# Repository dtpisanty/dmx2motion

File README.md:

# dmx2motion
An ESP32 based open-hardware project to control varing frequency AC motror drivers through DMX, ArtNet, OSC and MQTT

## Circuit board files
Schematics and PCB files were created using DIP Trace

## Library dependencies
This project uses Lukas Salomons ESP32-DMX Library https://github.com/luksal/ESP32-DMX and ThingPulse's ssd1306 OLED driver https://github.com/ThingPulse/esp8266-oled-ssd1306

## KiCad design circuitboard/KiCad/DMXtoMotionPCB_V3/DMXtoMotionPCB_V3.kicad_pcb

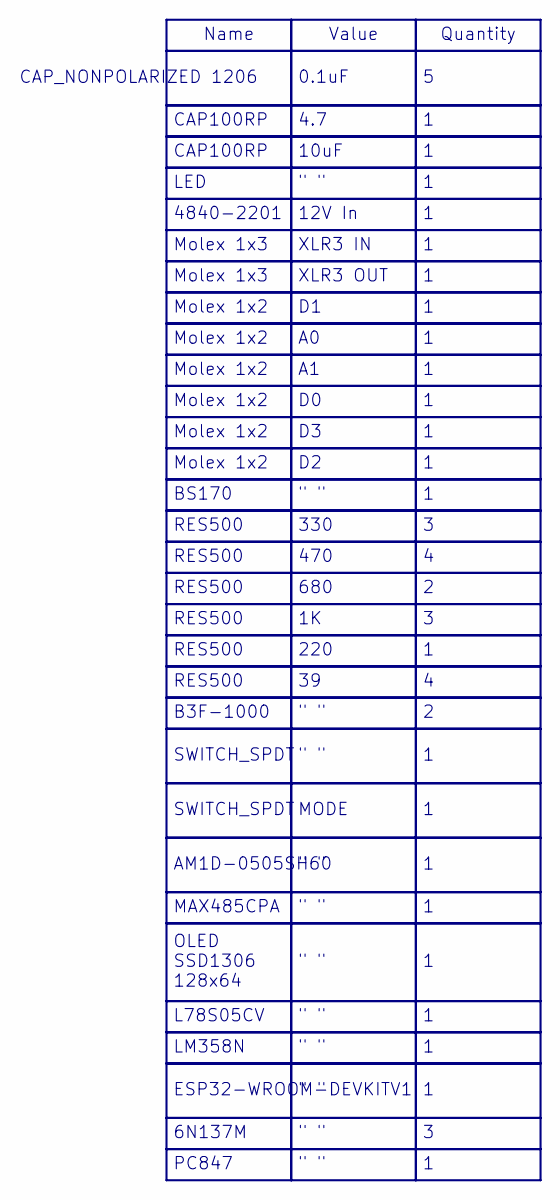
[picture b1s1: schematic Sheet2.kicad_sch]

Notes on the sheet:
Molex 1x2
" "
CAP100RP
470
L78S05CV
Molex 1x3
6N137M
Name
4840-2201
MAX485CPA
CAP_NONPOLARIZED 1206
RES500
4.7
Value
10uF
B3F-1000
AM1D-0505SH60
LM358N
330
PC847
680
220
0.1uF
LED
SWITCH_SPDT
XLR3 OUT
BS170
12V In
Quantity
MODE
XLR3 IN
OLED SSD1306 128x64
ESP32-WROOM-DEVKITV1

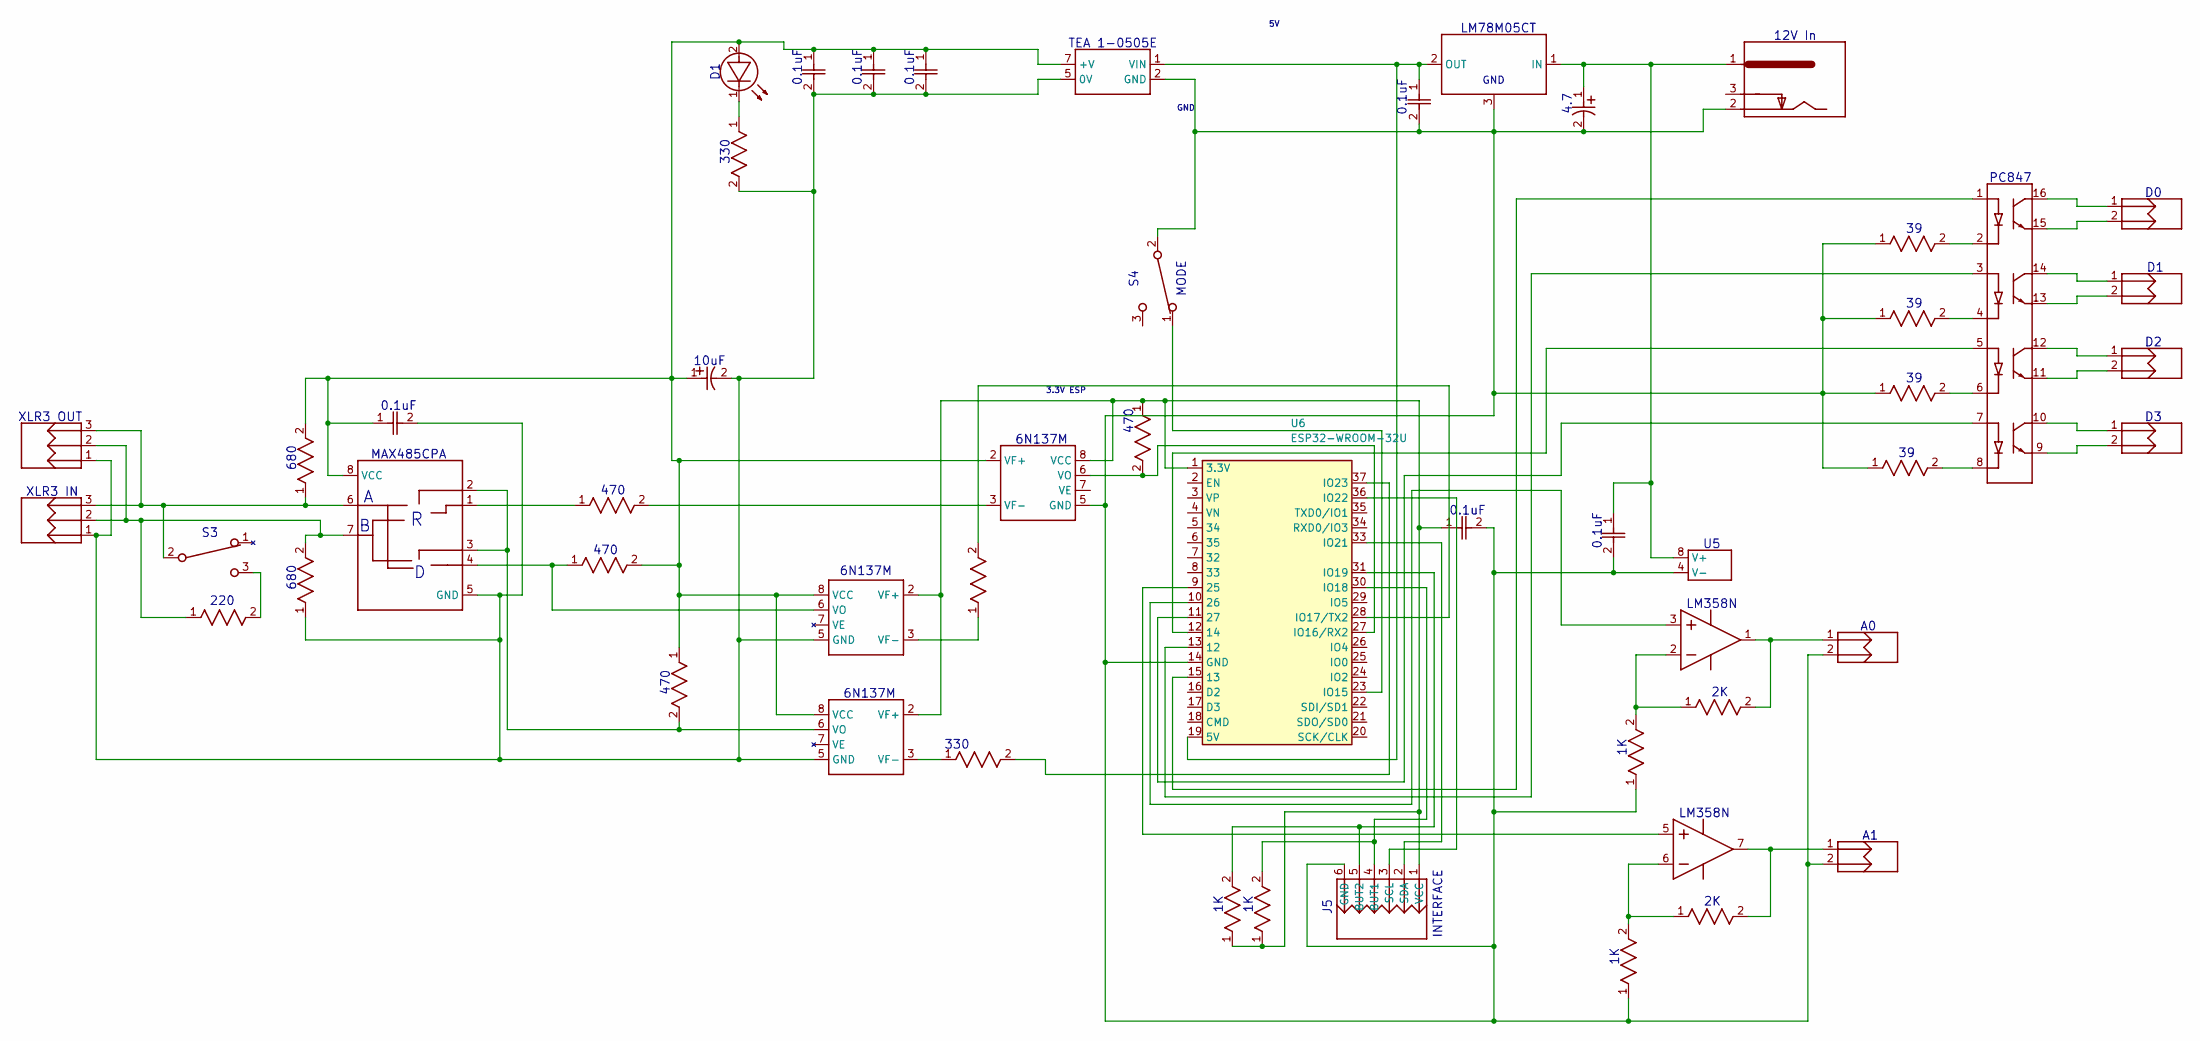
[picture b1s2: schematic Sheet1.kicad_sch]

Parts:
C1, C2, C3, C6, C7, C8, C9: 0.1uF; C_1206_3216Metric_Pad1.33x1.80mm_HandSolder
C4: 4.7; CP_Elec_4x5.3
C5: 10uF; CP_Elec_4x5.3
D1: LED; LED100
J1: 12V In; BarrelJack_Horizontal
J2: XLR3 IN; HDR-1X3
J3: XLR3 OUT; HDR-1X3
J4: D1; HDR-1X2
J5: INTERFACE; HDR-1X6
J6: A0; HDR-1X2
J7: A1; HDR-1X2
J8: D0; HDR-1X2
J9: D3; HDR-1X2
J10: D2; HDR-1X2
R1, R2, R3: 330; R_1206_3216Metric_Pad1.30x1.75mm_HandSolder
R4, R5, R6, R13: 470; R_1206_3216Metric_Pad1.30x1.75mm_HandSolder
R7, R8: 680; R_1206_3216Metric_Pad1.30x1.75mm_HandSolder
R9, R10, R18, R20: 1K; R_1206_3216Metric_Pad1.30x1.75mm_HandSolder
R12: 220; R_1206_3216Metric_Pad1.30x1.75mm_HandSolder
R14, R15, R16, R17: 39; R_1206_3216Metric_Pad1.30x1.75mm_HandSolder
R19, R21: 2K; R_1206_3216Metric_Pad1.30x1.75mm_HandSolder
S3: SWITCH_SPDT; HDRF-1X3T_2.54_8X3
S4: MODE; HDRF-1X3T_2.54_8X3
U1: AM1D-0505SH60; SIP-4(7)_19.5X6X2.54
U2: MAX485CPA; DIP-8
U4: LM78M05CT; TO-220V
U5: LM358N; DIP-8
U6: ESP32-WROOM-32U; ESP32-DevKitC
VO1, VO2, VO3: 6N137M; DIP-8
VO4: PC847; DIP-16

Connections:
3.3V_ESP: C7.1, J5.1 (VCC), R9.1 (A), R10.1 (A), R13.1 (A), U6.1 (3.3V), VO1.8 (VCC), VO2.2 (VF+), VO3.2 (VF+)
5V: C9.1, U1.1 (VIN), U4.2 (OUT), U6.19 (5V)
12V: C4.1 (PLUS), C6.1, J1.1, U4.1 (IN), U5.8 (V+)
But1: J5.4 (BUT1), R10.2 (B), U6.30 (IO18)
But2: J5.5 (BUT2), R9.2 (B), U6.31 (IO19)
GND: C4.2 (MINUS), C6.2, C7.2, C9.2, J1.2, J5.6 (GND), J6.2, J7.2, R14.1 (A), R15.1 (A), R16.1 (A), R17.1 (A), R18.1 (A), R20.1 (A), S4.2 (C1), U1.2 (GND), U4.3 (GND), U5.4 (V-), U6.14 (GND), U6.32 (GND), U6.38 (GND), VO1.5 (GND)
ISO-5V: C1.1, C2.1, C3.1, C5.1 (PLUS), C8.1, D1.2 (A), R5.2 (B), R6.1 (A), R7.2 (B), U1.7 (+V), U2.8 (VCC), VO1.2 (VF+), VO2.8 (VCC), VO3.8 (VCC)
ISO-GND: C1.2, C2.2, C3.2, C5.2 (MINUS), C8.2, J2.1, J3.1, R1.2 (B), R8.1 (A), U1.5 (0V), U2.5 (GND), VO2.5 (GND), VO3.5 (GND)
Net_0: R17.2 (B), VO4.2 (Cathode@1)
Net_1: U6.12 (14), VO4.5 (Anode@3)
Net_2: U6.11 (27), VO4.7 (Anode@4)
Net_4: D1.1 (K), R1.1 (A)
Net_6: U6.15 (13), VO4.1 (Anode@1)
Net_7: U6.13 (12), VO4.3 (Anode@2)
Net_8: U5.5 (IN+), U6.9 (25)
Net_9: R2.1 (A), VO2.3 (VF-)
Net_10: R3.2 (B), U6.37 (IO23)
Net_11: R3.1 (A), VO3.3 (VF-)
Net_12: R4.2 (B), VO1.3 (VF-)
Net_13: R4.1 (A), U2.1 (RO)
Net_14: R6.2 (B), U2.2 (~RE), U2.3 (DE), VO3.6 (VO)
Net_15: R5.1 (A), U2.4 (DI), VO2.6 (VO)
Net_16: J2.2, J3.2, R8.2 (B), R12.1 (A), U2.7 (B)
Net_17: J2.3, J3.3, R7.1 (A), S3.2 (C1), U2.6 (A)
Net_18: J7.1, R19.2 (B), U5.7 (OUT)
Net_21: R18.2 (B), R19.1 (A), U5.6 (IN-)
Net_22: S4.1 (C2), U6.23 (IO15)
Net_24: U5.3 (IN+), U6.10 (26)
Net_32: J5.2 (SDA), U6.33 (IO21)
Net_33: J5.3 (SCL), U6.36 (IO22)
Net_34: R12.2 (B), S3.3 (C3)
Net_35: R14.2 (B), VO4.4 (Cathode@2)
Net_36: R15.2 (B), VO4.6 (Cathode@3)
Net_37: R16.2 (B), VO4.8 (Cathode@4)
Net_38: J8.2, VO4.15 (Emitter@1)
Net_39: J8.1, VO4.16 (Collector@1)
Net_40: J4.1, VO4.14 (Collector@2)
Net_41: J4.2, VO4.13 (Emitter@2)
Net_42: J10.1, VO4.12 (Collector@3)
Net_43: J10.2, VO4.11 (Emitter@3)
Net_44: J9.1, VO4.10 (Collector@4)
Net_45: J9.2, VO4.9 (Emitter@4)
Net_46: J6.1, R21.2 (B), U5.1 (OUT)
Net_47: R20.2 (B), R21.1 (A), U5.2 (IN-)
RX: R13.2 (B), U6.27 (IO16/RX2), VO1.6 (VO)
TX: R2.2 (B), U6.28 (IO17/TX2)

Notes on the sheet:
PC847
330
6N137M
GND
0.1uF
10uF
470
XLR3 IN
XLR3 OUT
LM358N
MODE
TEA 1-0505E
680
INTERFACE
3.3V ESP
12V In
220
LM78M05CT
MAX485CPA
4.7

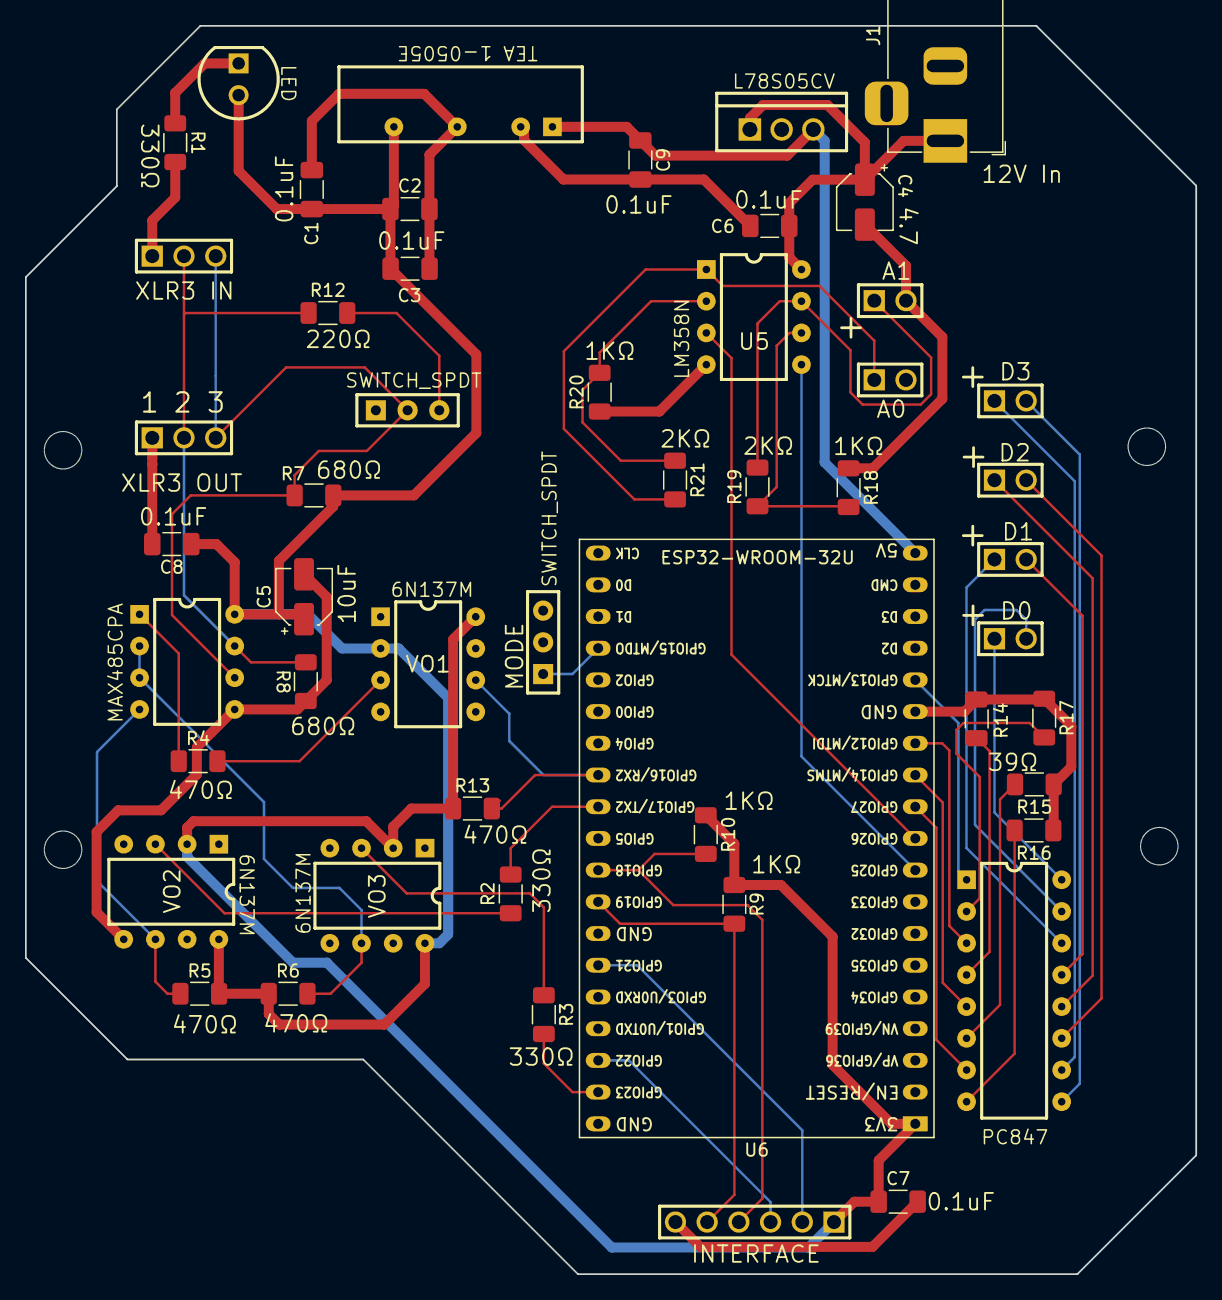
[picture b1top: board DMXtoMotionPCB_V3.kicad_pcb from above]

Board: 2 copper layers, 93.8 x 100.0 mm, 55 parts (0 on the bottom side), 46 nets.

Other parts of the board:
@HOLE0, @HOLE1, @HOLE2, @HOLE3: (no value)

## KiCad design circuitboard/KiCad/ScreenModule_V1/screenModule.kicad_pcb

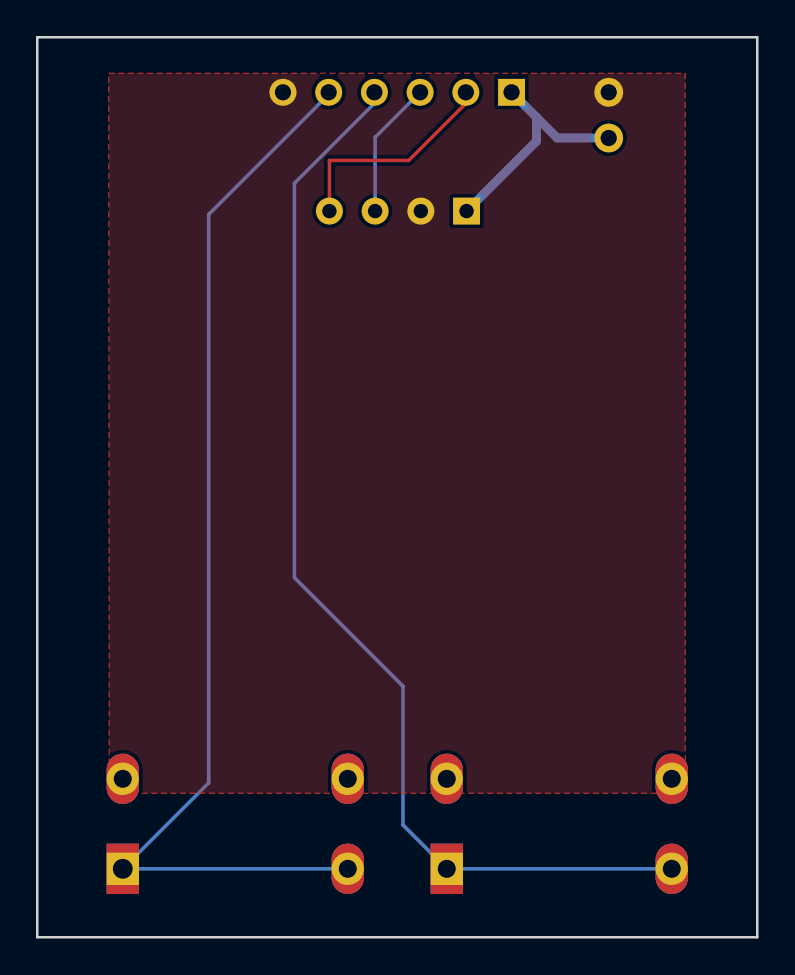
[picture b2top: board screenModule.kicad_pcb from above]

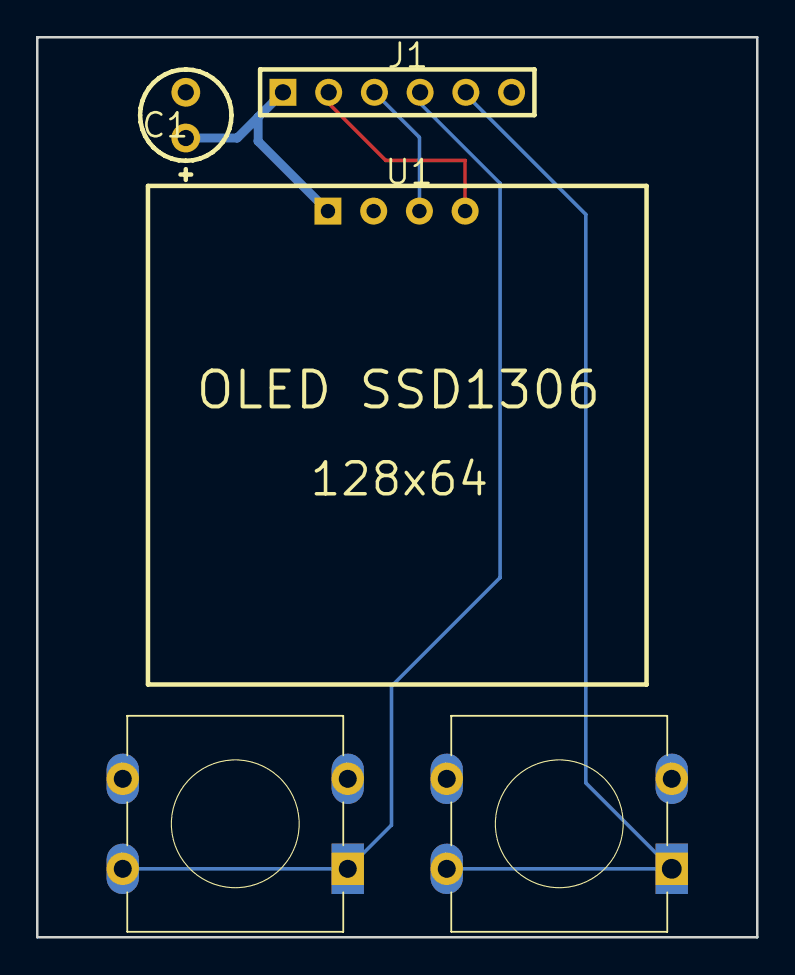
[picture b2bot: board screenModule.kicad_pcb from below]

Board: 2 copper layers, 40.0 x 50.0 mm, 11 parts (11 on the bottom side), 6 nets.

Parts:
C1: 4.7uF; CAPPR-2.54_5.08
J1: HDR-1X6; HDR-1x6
PAD1: PAD; PAD_PAD1
PAD2, PAD3, PAD4, PAD6, PAD7, PAD8: PAD; PAD_PAD2
PAD5: PAD
U1: OLED SSD1306 128X64; OLED_SSD1306

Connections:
Net_0: C1.2, J1.6, U1.2
Net_1: C1.1, J1.1, U1.1
Net_2: J1.2, U1.4
Net_3: J1.3, U1.3
Net_5: J1.5, PAD1.1, PAD2.2
Net_6: J1.4, PAD5.1, PAD6.2

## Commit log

2021-11-04 Modified the schematic to include the following features: * Added 2 additional digital outputs * Replaced relay output with BPJ optocoupler * Replaced PWM output with 2 DAC outputs passing through an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
2022-04-01 Finished designing and routing version 2
2022-04-01 removed useless files
2022-04-01 updated gerber files
2025-01-31 update files to latest version. MAJOR CHANGES
2025-02-01 Added KiCAD and Eagle PCB files. Updated KiCAD main board to V3
2025-02-04 Slight modifications on KiCAD V3 files. Generated fabrication files
2025-02-05 Changes of through hole diameters in KiCAD V3 and BOM
2025-02-05 KiCAD files
2025-02-05 lista de materiales semiactualizada
2025-02-05 double checked through holes and part names. Completed BOM
2025-02-05 trace adjustments
2025-02-06 Actualización de componentes obsoletos
2025-02-06 Actualización de lista de componentes
